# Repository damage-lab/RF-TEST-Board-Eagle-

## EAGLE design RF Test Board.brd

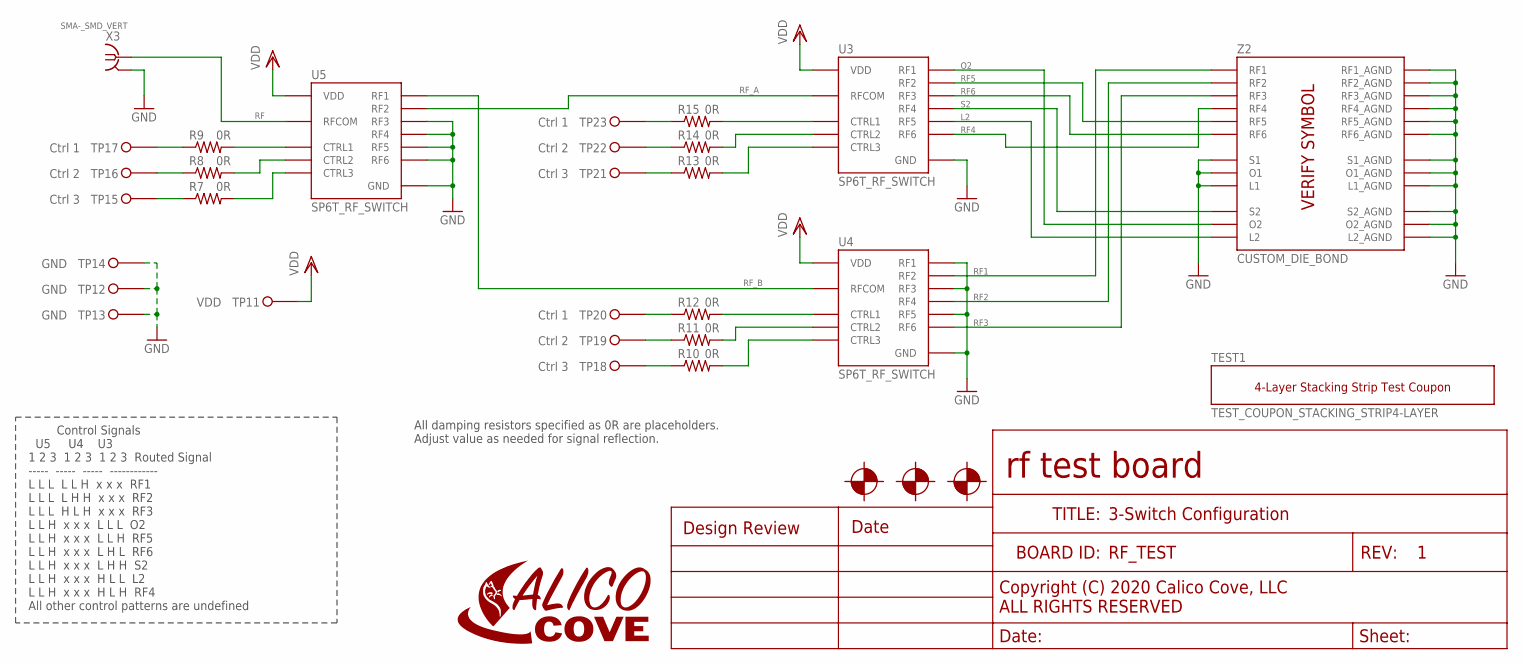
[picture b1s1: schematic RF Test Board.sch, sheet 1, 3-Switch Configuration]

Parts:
DOCBLOCK1: DOCBLOCK_REVIEW_2020; DOCBLOCK
FID$1, FID$2, FID$3: FIDUCIAL
LOGO1: LOGO_CC_SMALL; CC_FULL_SMALL
R7, R8, R9, R10, R11, R12, R13, R14, R15: 0R; 0603
TEST1: TEST_COUPON_STACKING_STRIP4-LAYER; TEST_COUPON_4-LAYER_STACKING_STRIP
TP11: VDD; TEST_POINT_TH
TP12, TP13, TP14: GND; TEST_POINT_TH
TP15, TP18, TP21: Ctrl 3; TEST_POINT_TH
TP16, TP19, TP22: Ctrl 2; TEST_POINT_TH
TP17, TP20, TP23: Ctrl 1; TEST_POINT_TH
U3, U4, U5: SP6T_RF_SWITCH; MT1817
X3: SMA-_SMD_VERT; LINX_SMD
Z2: CUSTOM_DIE_BOND; CUSTOM_IC_DIE_BOND

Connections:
GND: TP12.P$1, TP13.P$1, TP14.P$1, U3.PAD (GND), U3.PAD_VIA (GND), U4.1 (RF5), U4.2 (RF3), U4.3 (RF1), U4.PAD (GND), U4.PAD_VIA (GND), U5.1 (RF5), U5.2 (RF3), U5.10 (RF4), U5.11 (RF6), U5.PAD (GND), U5.PAD_VIA (GND), X3.GND1 (SHIELD), X3.GND2 (SHIELD), Z2.L1, Z2.L1_GND1 (L1_AGND), Z2.L1_GND2 (L1_AGND), Z2.L2_GND1 (L2_AGND), Z2.L2_GND2 (L2_AGND), Z2.O1, Z2.O1_GND1 (O1_AGND), Z2.O1_GND2 (O1_AGND), Z2.O2_GND1 (O2_AGND), Z2.O2_GND2 (O2_AGND), Z2.RF1_GND1 (RF1_AGND), Z2.RF1_GND2 (RF1_AGND), Z2.RF2_GND1 (RF2_AGND), Z2.RF2_GND2 (RF2_AGND), Z2.RF3_GND1 (RF3_AGND), Z2.RF3_GND2 (RF3_AGND), Z2.RF4_GND1 (RF4_AGND), Z2.RF4_GND2 (RF4_AGND), Z2.RF5_GND1 (RF5_AGND), Z2.RF5_GND2 (RF5_AGND), Z2.RF6_GND1 (RF6_AGND), Z2.RG6_GND2 (RF6_AGND), Z2.S1, Z2.S1_GND1 (S1_AGND), Z2.S1_GND2 (S1_AGND), Z2.S2_GND1 (S2_AGND), Z2.S2_GND2 (S2_AGND); also elsewhere on the board
L2: U3.1 (RF5), Z2.L2
unnamed: R15.P$1 (1), TP23.P$1
unnamed: R14.P$1 (1), TP22.P$1
unnamed: R13.P$1 (1), TP21.P$1
unnamed: R15.P$2 (2), U3.7 (CTRL1)
unnamed: R13.P$2 (2), U3.5 (CTRL3)
unnamed: R14.P$2 (2), U3.6 (CTRL2)
unnamed: R9.P$1 (1), TP17.P$1
unnamed: R8.P$1 (1), TP16.P$1
unnamed: R7.P$1 (1), TP15.P$1
unnamed: R12.P$1 (1), TP20.P$1
unnamed: R11.P$1 (1), TP19.P$1
unnamed: R10.P$1 (1), TP18.P$1
unnamed: R9.P$2 (2), U5.7 (CTRL1)
unnamed: R8.P$2 (2), U5.6 (CTRL2)
unnamed: R7.P$2 (2), U5.5 (CTRL3)
unnamed: R12.P$2 (2), U4.7 (CTRL1)
unnamed: R10.P$2 (2), U4.5 (CTRL3)
unnamed: R11.P$2 (2), U4.6 (CTRL2)
O2: U3.3 (RF1), Z2.O2
RF: U5.13 (RFCOM), X3.1
RF1: U4.9 (RF2), Z2.RF1
RF2: U4.10 (RF4), Z2.RF2
RF3: U4.11 (RF6), Z2.RF3
RF4: U3.11 (RF6), Z2.RF4
RF5: U3.9 (RF2), Z2.RF5
RF6: U3.2 (RF3), Z2.RF6
RF_A: U3.13 (RFCOM), U5.9 (RF2)
RF_B: U4.13 (RFCOM), U5.3 (RF1)
S2: U3.10 (RF4), Z2.S2
VDD: TP11.P$1, U3.4 (VDD), U4.4 (VDD), U5.4 (VDD)

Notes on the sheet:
3-Switch Configuration
All damping resistors specified as 0R are placeholders. Adjust value as needed for signal reflection.
Control Signals U5 U4 U3 1 2 3 1 2 3 1 2 3 Routed Signal ----- ----- ----- ------------ L L L L L H x x x RF1 L L L L H H x x x RF2 L L L H L H x x x RF3 L L H x x x L L L O2 L L H x x x L L H RF5 L L H x x x L H L RF6 L L H x x x L H H S2 L L H x x x H L L L2 L L H x x x H L H RF4 All other contro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

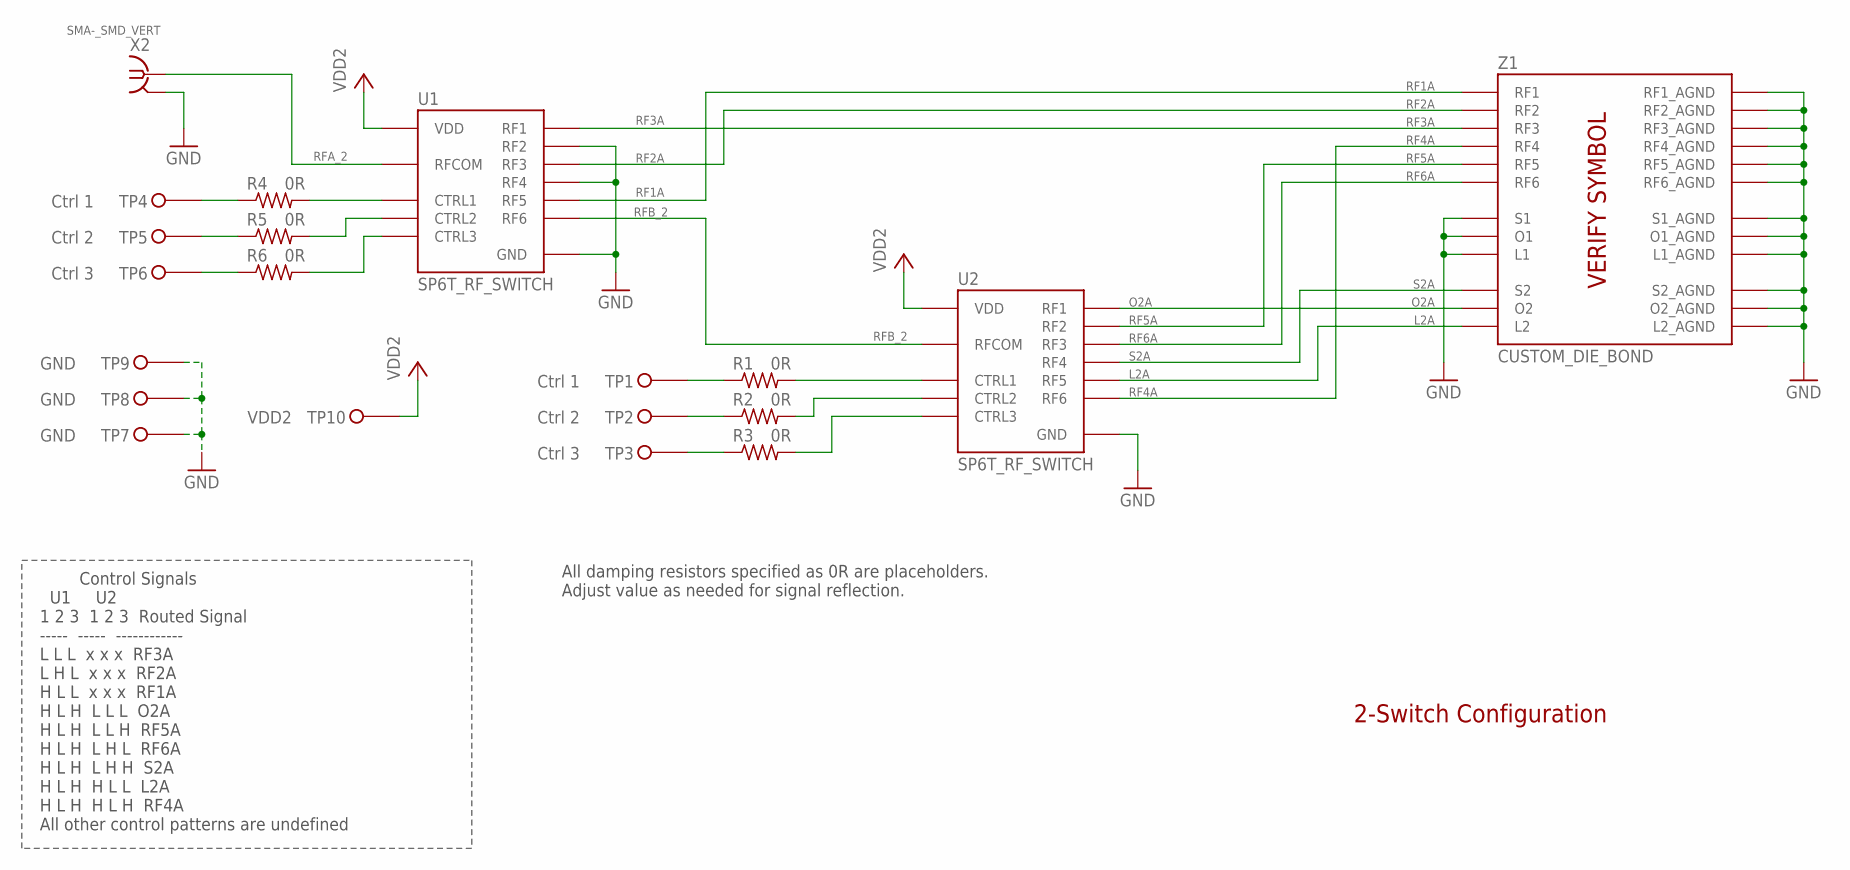
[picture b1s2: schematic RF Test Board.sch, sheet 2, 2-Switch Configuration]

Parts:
R1, R2, R3, R4, R5, R6: 0R; 0603
TP1, TP4: Ctrl 1; TEST_POINT_TH
TP2, TP5: Ctrl 2; TEST_POINT_TH
TP3, TP6: Ctrl 3; TEST_POINT_TH
TP7, TP8, TP9: GND; TEST_POINT_TH
TP10: VDD2; TEST_POINT_TH
U1, U2: SP6T_RF_SWITCH; MT1817
X2: SMA-_SMD_VERT; LINX_SMD
Z1: CUSTOM_DIE_BOND; CUSTOM_IC_DIE_BOND

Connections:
GND: TP7.P$1, TP8.P$1, TP9.P$1, U1.9 (RF2), U1.10 (RF4), U1.PAD (GND), U1.PAD_VIA (GND), U2.PAD (GND), U2.PAD_VIA (GND), X2.GND1 (SHIELD), X2.GND2 (SHIELD), Z1.L1, Z1.L1_GND1 (L1_AGND), Z1.L1_GND2 (L1_AGND), Z1.L2_GND1 (L2_AGND), Z1.L2_GND2 (L2_AGND), Z1.O1, Z1.O1_GND1 (O1_AGND), Z1.O1_GND2 (O1_AGND), Z1.O2_GND1 (O2_AGND), Z1.O2_GND2 (O2_AGND), Z1.RF1_GND1 (RF1_AGND), Z1.RF1_GND2 (RF1_AGND), Z1.RF2_GND1 (RF2_AGND), Z1.RF2_GND2 (RF2_AGND), Z1.RF3_GND1 (RF3_AGND), Z1.RF3_GND2 (RF3_AGND), Z1.RF4_GND1 (RF4_AGND), Z1.RF4_GND2 (RF4_AGND), Z1.RF5_GND1 (RF5_AGND), Z1.RF5_GND2 (RF5_AGND), Z1.RF6_GND1 (RF6_AGND), Z1.RG6_GND2 (RF6_AGND), Z1.S1, Z1.S1_GND1 (S1_AGND), Z1.S1_GND2 (S1_AGND), Z1.S2_GND1 (S2_AGND), Z1.S2_GND2 (S2_AGND); also elsewhere on the board
L2A: U2.1 (RF5), Z1.L2
unnamed: R4.P$1 (1), TP4.P$1
unnamed: R5.P$1 (1), TP5.P$1
unnamed: R6.P$1 (1), TP6.P$1
unnamed: R1.P$1 (1), TP1.P$1
unnamed: R2.P$1 (1), TP2.P$1
unnamed: R3.P$1 (1), TP3.P$1
unnamed: R4.P$2 (2), U1.7 (CTRL1)
unnamed: R5.P$2 (2), U1.6 (CTRL2)
unnamed: R6.P$2 (2), U1.5 (CTRL3)
unnamed: R1.P$2 (2), U2.7 (CTRL1)
unnamed: R3.P$2 (2), U2.5 (CTRL3)
unnamed: R2.P$2 (2), U2.6 (CTRL2)
O2A: U2.3 (RF1), Z1.O2
RF1A: U1.1 (RF5), Z1.RF1
RF2A: U1.2 (RF3), Z1.RF2
RF3A: U1.3 (RF1), Z1.RF3
RF4A: U2.11 (RF6), Z1.RF4
RF5A: U2.9 (RF2), Z1.RF5
RF6A: U2.2 (RF3), Z1.RF6
RFA_2: U1.13 (RFCOM), X2.1
RFB_2: U1.11 (RF6), U2.13 (RFCOM)
S2A: U2.10 (RF4), Z1.S2
VDD2: TP10.P$1, U1.4 (VDD), U2.4 (VDD)

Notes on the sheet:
2-Switch Configuration
All damping resistors specified as 0R are placeholders. Adjust value as needed for signal reflection.
Control Signals U1 U2 1 2 3 1 2 3 Routed Signal ----- ----- ------------ L L L x x x RF3A L H L x x x RF2A H L L x x x RF1A H L H L L L O2A H L H L L H RF5A H L H L H L RF6A H L H L H H S2A H L H H L L L2A H L H H L H RF4A All other control patterns are undefined

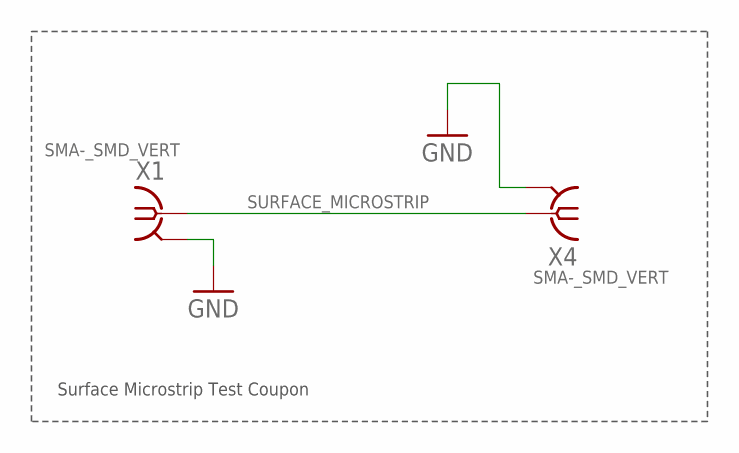
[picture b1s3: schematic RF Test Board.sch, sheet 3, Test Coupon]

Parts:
X1, X4: SMA-_SMD_VERT; LINX_SMD

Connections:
GND: X1.GND1 (SHIELD), X1.GND2 (SHIELD), X4.GND1 (SHIELD), X4.GND2 (SHIELD); also elsewhere on the board
SURFACE_MICROSTRIP: X1.1, X4.1

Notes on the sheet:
Surface Microstrip Test Coupon

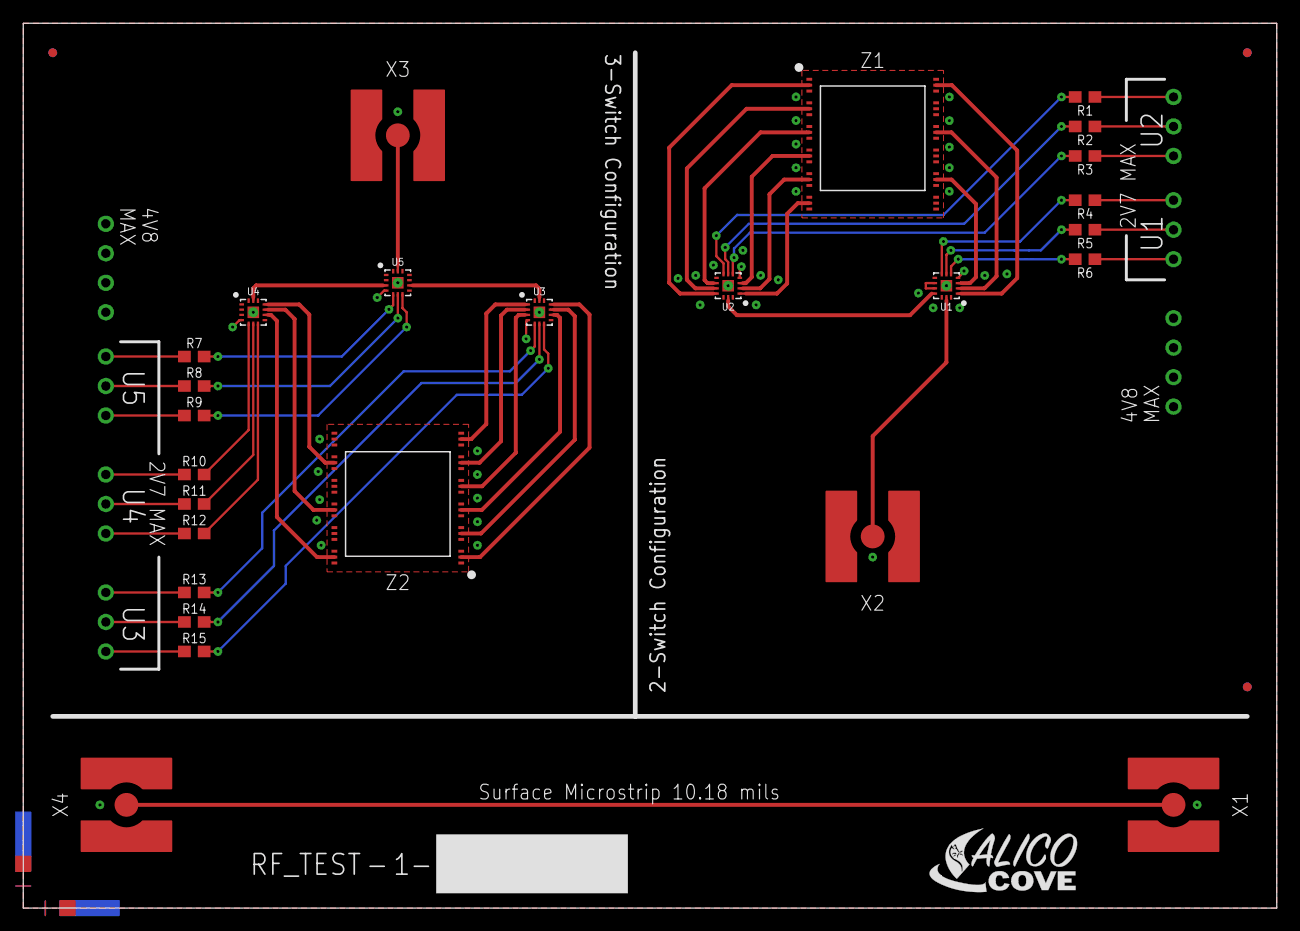
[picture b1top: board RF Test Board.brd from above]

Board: 4 copper layers, 108.0 x 76.2 mm, 55 parts (0 on the bottom side), 57 nets.

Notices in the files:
parts and their libraries:
CalicoCove: Copyright (C) 2020 Calico Cove, LLC
ALL RIGHTS RESERVED
